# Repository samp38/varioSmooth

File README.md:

# VarioSmooth

Lightweight, solar powered, helmet embedded audio variometer for free flight.

- [**v1**](v1/README.md) (2017): PIC24F16KA101 + MS5611, LTC4071 solar charger, 22 × 17 mm PCB. Firmware (MPLAB X / XC16), PCB (Eagle, ported to KiCad 10), docs and open issues.
- [**v2**](v2/README.md) (in progress): nRF52840 (Raytac MDBT50Q) with Bluetooth LE, sends barometric altitude and vario to XCTrack / LK8000. Firmware with PlatformIO, flex PCB.

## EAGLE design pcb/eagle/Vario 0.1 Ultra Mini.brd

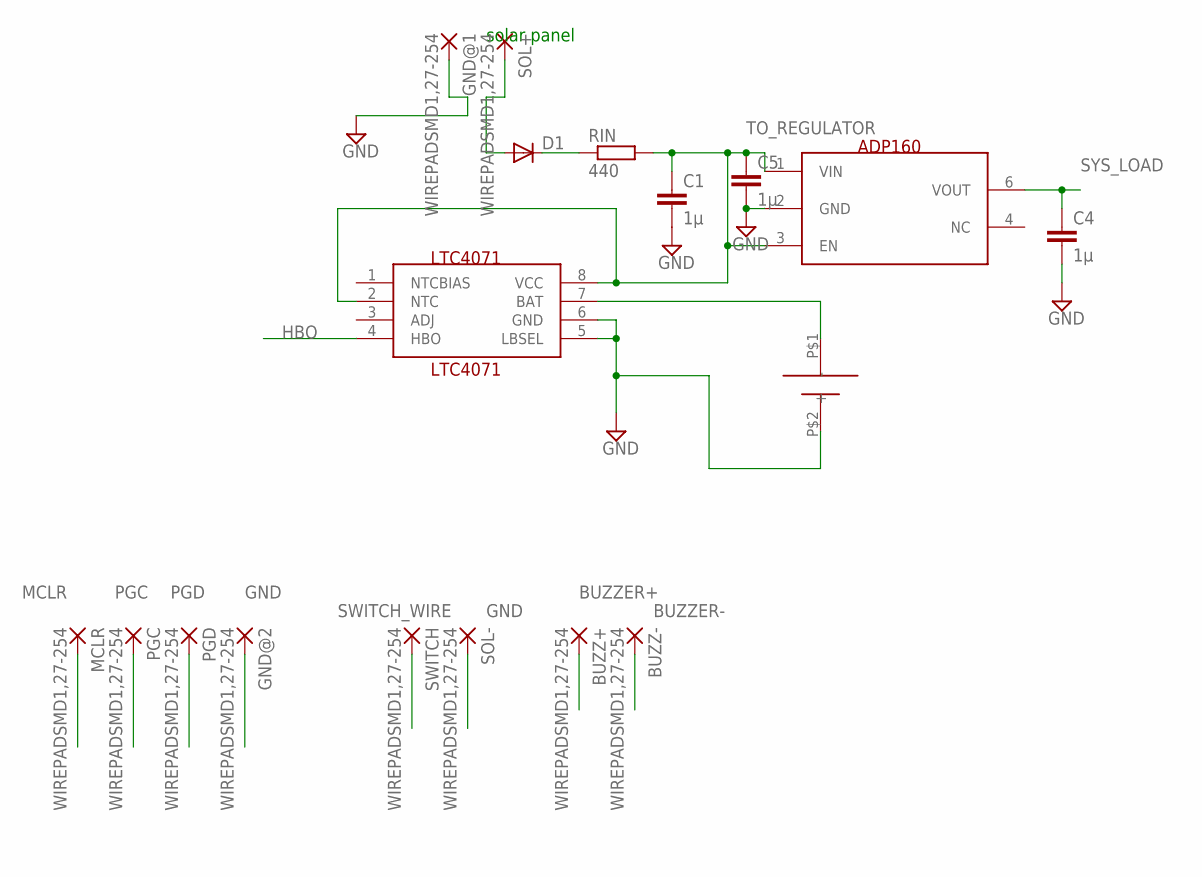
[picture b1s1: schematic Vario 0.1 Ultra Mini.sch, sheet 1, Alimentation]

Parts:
ADP160: ADP160/161/162/163; TSOT23-6_DDC
BATT+: VARIO_LIPO
BUZZ+: WIREPADSMD1,27-254; SMD1,27-2,54
BUZZ-: WIREPADSMD1,27-254; SMD1,27-2,54
C1, C4, C5: 1µ; C0603
D1: DIODE-SOD323-R; SOD323-R
GND@1, GND@2: WIREPADSMD1,27-254; SMD1,27-2,54
LTC4071: LTC4071; MSOP8
MCLR: WIREPADSMD1,27-254; SMD1,27-2,54
PGC: WIREPADSMD1,27-254; SMD1,27-2,54
PGD: WIREPADSMD1,27-254; SMD1,27-2,54
RIN: 440; R0603
SOL+: WIREPADSMD1,27-254; SMD1,27-2,54
SOL-: WIREPADSMD1,27-254; SMD1,27-2,54
SWITCH: WIREPADSMD1,27-254; SMD1,27-2,54

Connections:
BATT: BATT+.P$1 (+), LTC4071.7 (BAT)
BUZZER+: BUZZ+.1; also elsewhere on the board
BUZZER-: BUZZ-.1; also elsewhere on the board
GND: ADP160.2 (GND), BATT+.P$2 (-), C1.2, C4.2, C5.2, GND@1.1, GND@2.1, LTC4071.5 (LBSEL), LTC4071.6 (GND), SOL-.1; also elsewhere on the board
HBO: LTC4071.4 (HBO)
MCLR: MCLR.1; also elsewhere on the board
unnamed: D1.C, RIN.1
PGC: PGC.1; also elsewhere on the board
PGD: PGD.1; also elsewhere on the board
SOL+: D1.A, SOL+.1
SWITCH_WIRE: SWITCH.1; also elsewhere on the board
SYS_LOAD: ADP160.6 (VOUT), C4.1; also elsewhere on the board
TO_REGULATOR: ADP160.1 (VIN), ADP160.3 (EN), C1.1, C5.1, LTC4071.2 (NTC), LTC4071.8 (VCC), RIN.2

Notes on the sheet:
solar panel

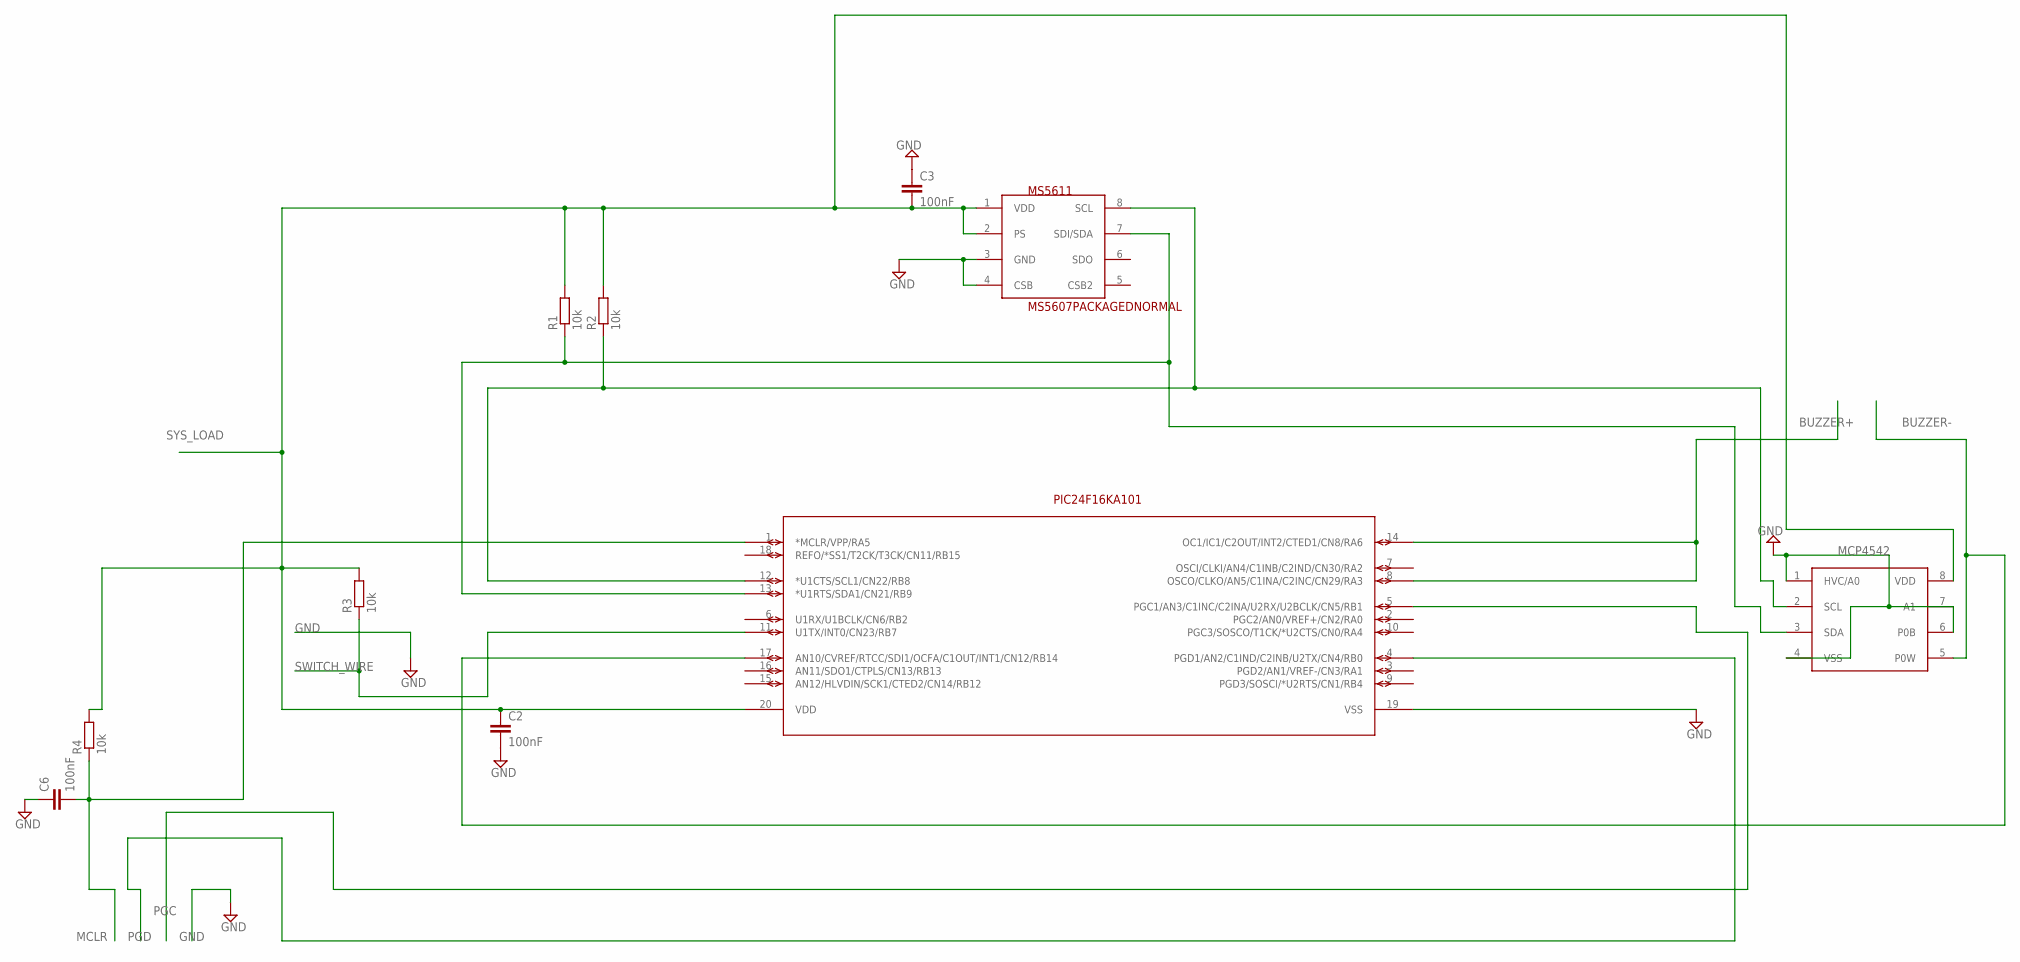
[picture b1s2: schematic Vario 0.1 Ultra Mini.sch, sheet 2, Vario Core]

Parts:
C2, C3, C6: 100nF; C0603
MCP4542: MCP4542; MSOP8
MS5611: MS5607PACKAGEDNORMAL; MS5607-02BA03
PIC24F16KA101: PIC24F16KA101-X_; SSOP20_MC
R1, R2, R3, R4: 10k; R0603

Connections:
BUZZER+: PIC24F16KA101.8 (OSCO/CLKO/AN5/C1INA/C2INC/CN29/RA3), PIC24F16KA101.14 (OC1/IC1/C2OUT/INT2/CTED1/CN8/RA6); also elsewhere on the board
BUZZER-: MCP4542.5 (P0W), PIC24F16KA101.17 (AN10/CVREF/RTCC/SDI1/OCFA/C1OUT/INT1/CN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); also elsewhere on the board
GND: C2.2, C3.1, C6.1, MCP4542.1 (HVC/A0), MCP4542.4 (VSS), MCP4542.6 (P0B), MCP4542.7 (A1), MS5611.3 (GND), MS5611.4 (CSB), PIC24F16KA101.19 (VSS); also elsewhere on the board
MCLR: C6.2, PIC24F16KA101.1 (*MCLR/VPP/RA5), R4.1; also elsewhere on the board
PGC: PIC24F16KA101.5 (PGC1/AN3/C1INC/C2INA/U2RX/U2BCLK/CN5/RB1); also elsewhere on the board
PGD: PIC24F16KA101.4 (PGD1/AN2/C1IND/C2INB/U2TX/CN4/RB0); also elsewhere on the board
SCL: MCP4542.2 (SCL), MS5611.8 (SCL), PIC24F16KA101.12 (*U1CTS/SCL1/CN22/RB8), R2.1
SDA: MCP4542.3 (SDA), MS5611.7 (SDI/SDA), PIC24F16KA101.13 (*U1RTS/SDA1/CN21/RB9), R1.1
SWITCH_WIRE: PIC24F16KA101.11 (U1TX/INT0/CN23/RB7), R3.1; also elsewhere on the board
SYS_LOAD: C2.1, C3.2, MCP4542.8 (VDD), MS5611.1 (VDD), MS5611.2 (PS), PIC24F16KA101.20 (VDD), R1.2, R2.2, R3.2, R4.2; also elsewhere on the board

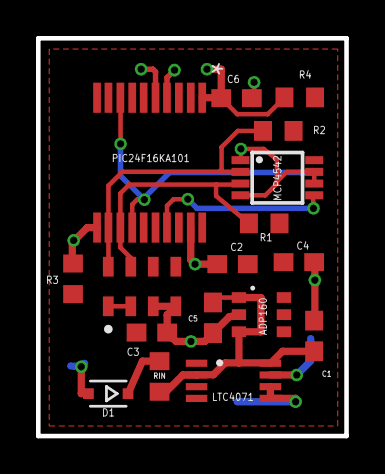
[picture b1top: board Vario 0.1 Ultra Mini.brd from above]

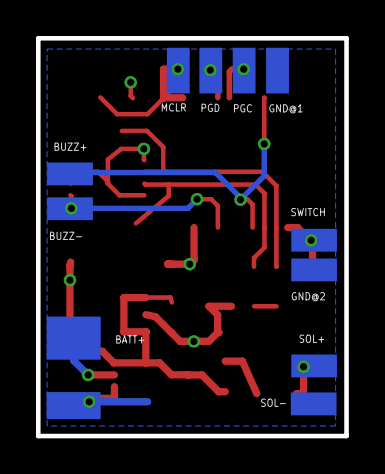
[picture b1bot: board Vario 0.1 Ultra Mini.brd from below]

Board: 2 copper layers, 17.1 x 22.1 mm, 28 parts (11 on the bottom side), 14 nets.

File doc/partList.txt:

Partlist

Exported from Vario 0.1 Ultra Mini.brd at 05/06/2018 13:43

EAGLE Version 7.3.0 Copyright (c) 1988-2015 CadSoft

Assembly variant: 

Part          Value                Package       Library                 

R1            10k                  R0603         rcl                     
R2            10k                  R0603         rcl                     
R3            10k                  R0603         rcl                     
R4            10k                  R0603         rcl                     
RIN           440                  R0603         rcl                     
C1            1µ                   C0603         rcl                     
C2            100nF                C0603         rcl                     
C3            100nF                C0603         rcl                     
C4            1µ                   C0603         rcl                     
C5            1µ                   C0603         rcl                     
C6            100nF                C0603         rcl                     
D1            1PS76SB10            SOD323-R      Nexperia                
ADP160        2.8 or 3V            TSOT23-6_DDC  analog-devices          
LTC4071       LTC4071              MSOP8         linear-technology       
MCP4542       MCP4542              MSOP8         microchip               
MS5611        MS5607               MS5607-02BA03 measurement_specialties 
PIC24F16KA101                      SSOP20_MC     microchip               
BUZZER        KPEG006                            kingstate

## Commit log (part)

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2017-09-06 remove old backup files
2018-06-04 Doc
    Doc
2018-06-05 gitignore
